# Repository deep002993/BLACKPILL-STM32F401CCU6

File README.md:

Title: BlackPill STM32F401CCU6 KiCad PCB Design

Description:
This repository hosts a KiCad PCB design for the STM32F401CCU6 microcontroller board, commonly known as BlackPill. Featuring a meticulously crafted layout and detailed schematic, it's optimized for affordability and performance, ideal for embedded projects. With comprehensive documentation and open-source licensing, it's ready for seamless integration and customization in your designs.

Features:
- Detailed Schematic & Layout
- Component Libraries Included
- Comprehensive Documentation
- Open Source & Customizable

Get Started:
Clone or download the repository to access the design files. Integrate seamlessly into your KiCad projects and customize as needed. Join the community to contribute or seek assistance.

Let's innovate with BlackPill STM32F401CCU6 KiCad PCB design!

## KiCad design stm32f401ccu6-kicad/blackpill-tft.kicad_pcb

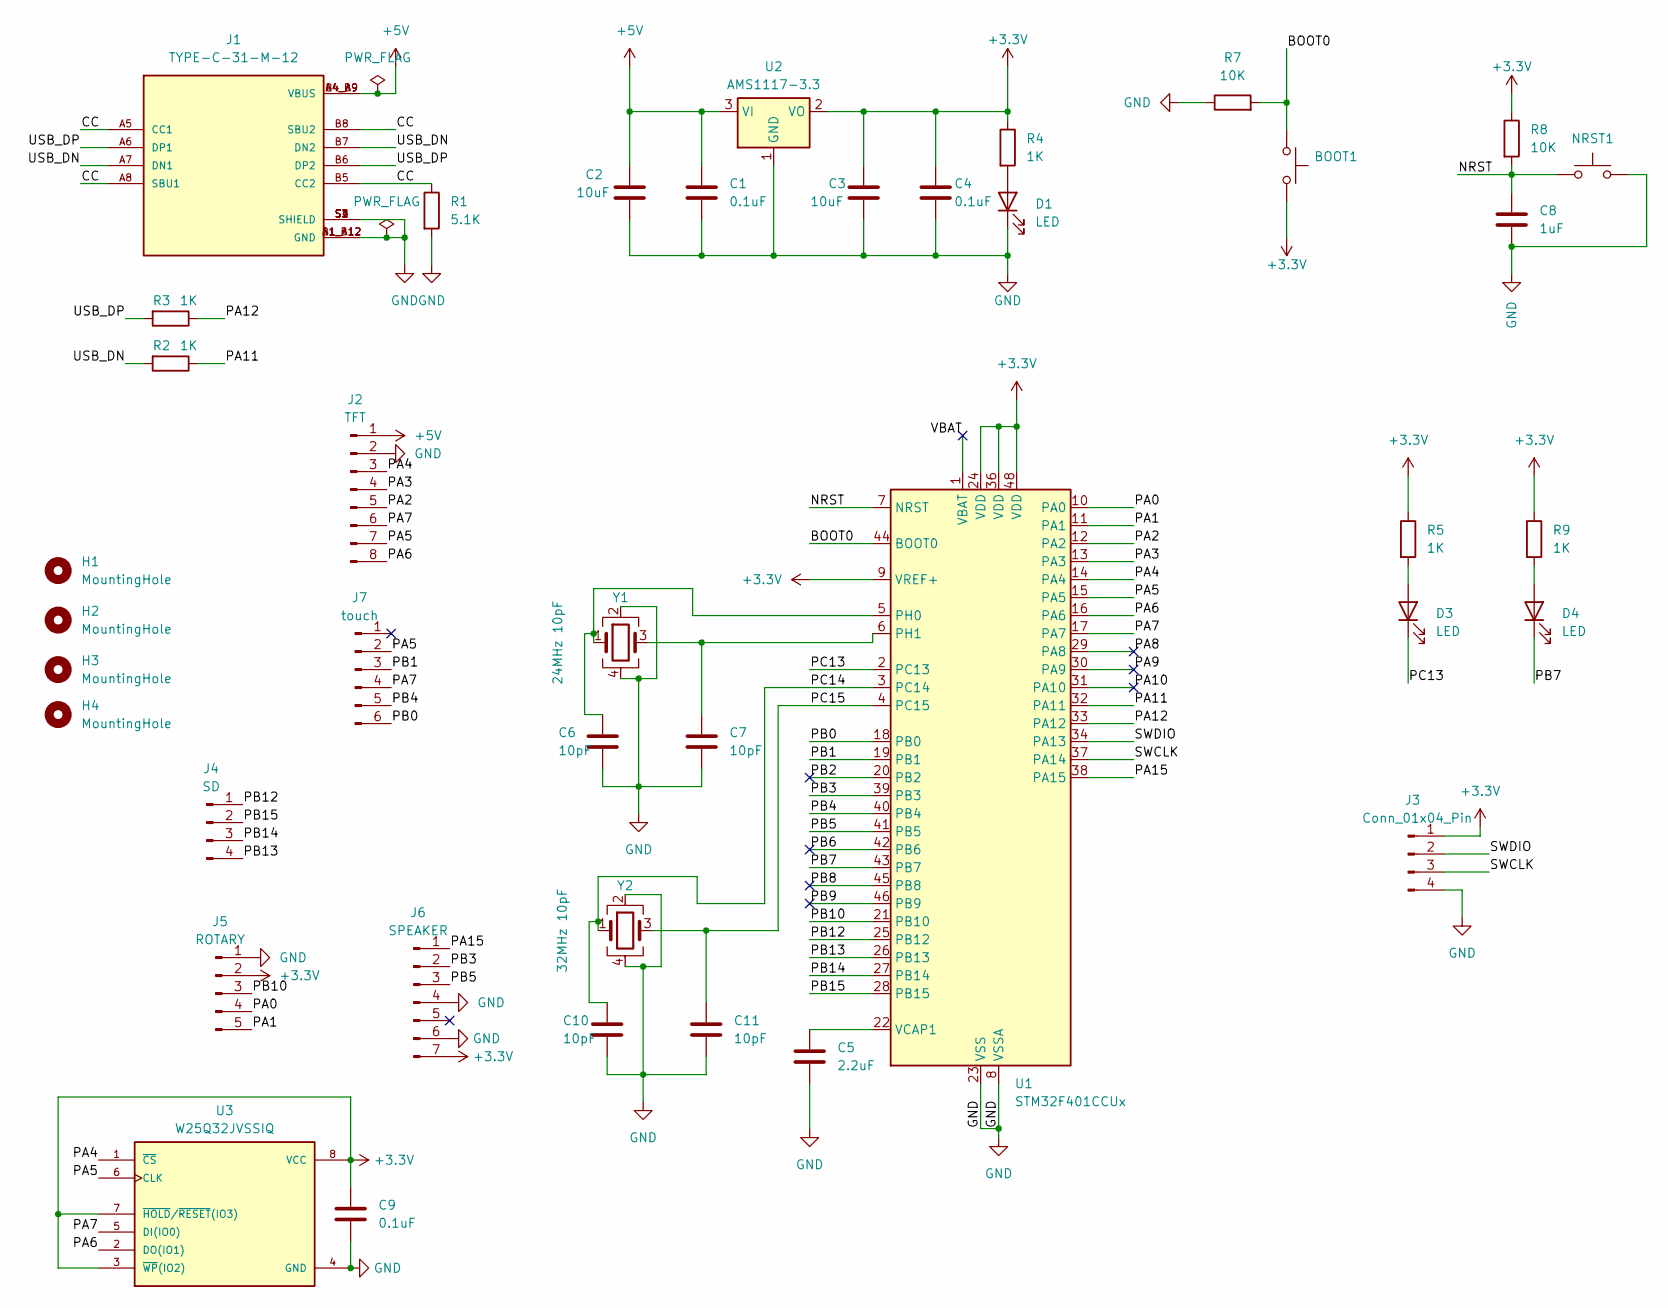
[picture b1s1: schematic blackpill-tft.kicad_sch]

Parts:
BOOT1: SW_DIP_x01; SW_Push_SPST_NO_Alps_0306
C1, C4, C9: 0.1uF; C_0805_2012Metric
C2, C3: 10uF; C_0805_2012Metric
C5: 2.2uF; C_0805_2012Metric
C6, C7, C10, C11: 10pF; C_0805_2012Metric
C8: 1uF; C_0805_2012Metric
D1, D3, D4: LED; LED_0805_2012Metric
H1, H2, H3, H4: MountingHole; MountingHole_2.2mm_M2
J1: TYPE-C-31-M-12; HRO_TYPE-C-31-M-12; PARTREV 2020.12.08
J2: TFT; PinHeader_1x08_P2.54mm_Vertical
J3: Conn_01x04_Pin; PinHeader_1x04_P2.54mm_Vertical
J4: SD; PinSocket_1x04_P2.54mm_Vertical
J5: ROTARY; PinHeader_1x05_P2.54mm_Vertical
J6: SPEAKER; PinHeader_1x07_P2.54mm_Vertical
J7: touch; PinHeader_1x06_P2.54mm_Vertical
NRST1: SW_DIP_x01; SW_Push_SPST_NO_Alps_0306
R1: 5.1K; R_0805_2012Metric
R2, R3, R4, R5, R9: 1K; R_0805_2012Metric
R7, R8: 10K; R_0805_2012Metric
U1: STM32F401CCUx; LQFP-48-1EP_7x7mm_P0.5mm_EP3.6x3.6mm
U2: AMS1117-3.3; SOT-223-3_TabPin2
U3: W25Q32JVSSIQ; SOIC127P790X216-8N
Y1: 24MHz 10pF; OSC_XRCGB24M000F2P01R0
Y2: 32MHz 10pF; OSC_XRCGB24M000F2P01R0

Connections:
+3.3V: BOOT1.2, C3.1, C4.1, C9.1, J3.1, J5.2, J6.7, R4.1, R5.1, R8.1, R9.1, U1.9 (VREF+), U1.24 (VDD), U1.36 (VDD), U1.48 (VDD), U2.2 (VO), U3.3 (~WP(IO2)), U3.7 (~HOLD/~RESET(IO3)), U3.8 (VCC)
+5V: C1.1, C2.1, J1.A4_B9 (VBUS), J1.B4_A9 (VBUS), J2.1, U2.3 (VI)
/BOOT0: BOOT1.1, R7.2, U1.44 (BOOT0)
/CC: J1.A5 (CC1), J1.A8 (SBU1), J1.B5 (CC2), J1.B8 (SBU2), R1.1
/NRST: C8.1, NRST1.1, R8.2, U1.7 (NRST)
/PA0: J5.4, U1.10 (PA0)
/PA1: J5.5, U1.11 (PA1)
/PA2: J2.5, U1.12 (PA2)
/PA3: J2.4, U1.13 (PA3)
/PA4: J2.3, U1.14 (PA4), U3.1 (~CS)
/PA5: J2.7, J7.2, U1.15 (PA5), U3.6 (CLK)
/PA6: J2.8, U1.16 (PA6), U3.2 (DO(IO1))
/PA7: J2.6, J7.4, U1.17 (PA7), U3.5 (DI(IO0))
/PA8: U1.29 (PA8)
/PA9: U1.30 (PA9)
/PA10: U1.31 (PA10)
/PA11: R2.1, U1.32 (PA11)
/PA12: R3.1, U1.33 (PA12)
/PA15: J6.1, U1.38 (PA15)
/PB0: J7.6, U1.18 (PB0)
/PB1: J7.3, U1.19 (PB1)
/PB2: U1.20 (PB2)
/PB3: J6.2, U1.39 (PB3)
/PB4: J7.5, U1.40 (PB4)
/PB5: J6.3, U1.41 (PB5)
/PB6: U1.42 (PB6)
/PB7: D4.1 (K), U1.43 (PB7)
/PB8: U1.45 (PB8)
/PB9: U1.46 (PB9)
/PB10: J5.3, U1.21 (PB10)
/PB12: J4.1, U1.25 (PB12)
/PB13: J4.4, U1.26 (PB13)
/PB14: J4.3, U1.27 (PB14)
/PB15: J4.2, U1.28 (PB15)
/PC13: D3.1 (K), U1.2 (PC13)
/PC14: C10.1, U1.3 (PC14), Y2.1
/PC15: C11.1, U1.4 (PC15), Y2.3
/SWCLK: J3.3, U1.37 (PA14)
/SWDIO: J3.2, U1.34 (PA13)
/USB_DN: J1.A7 (DN1), J1.B7 (DN2), R2.2
/USB_DP: J1.A6 (DP1), J1.B6 (DP2), R3.2
/VBAT: U1.1 (VBAT)
GND: C1.2, C2.2, C3.2, C4.2, C5.2, C6.2, C7.2, C8.2, C9.2, C10.2, C11.2, D1.1 (K), J1.A1_B12 (GND), J1.B1_A12 (GND), J1.S1 (SHIELD), J1.S2 (SHIELD), J1.S3 (SHIELD), J1.S4 (SHIELD), J2.2, J3.4, J5.1, J6.4, J6.6, NRST1.2, R1.2, R7.1, U1.8 (VSSA), U1.23 (VSS), U1.35 (VSS), U1.47 (VSS), U1.49 (VSS), U2.1 (GND), U3.4 (GND), Y1.2, Y1.4, Y2.2, Y2.4
unnamed: D1.2 (A), R4.2
unnamed: D3.2 (A), R5.2
unnamed: D4.2 (A), R9.2
unnamed: C6.1, U1.5 (PH0), Y1.1
unnamed: C7.1, U1.6 (PH1), Y1.3
unnamed: C5.1, U1.22 (VCAP1)

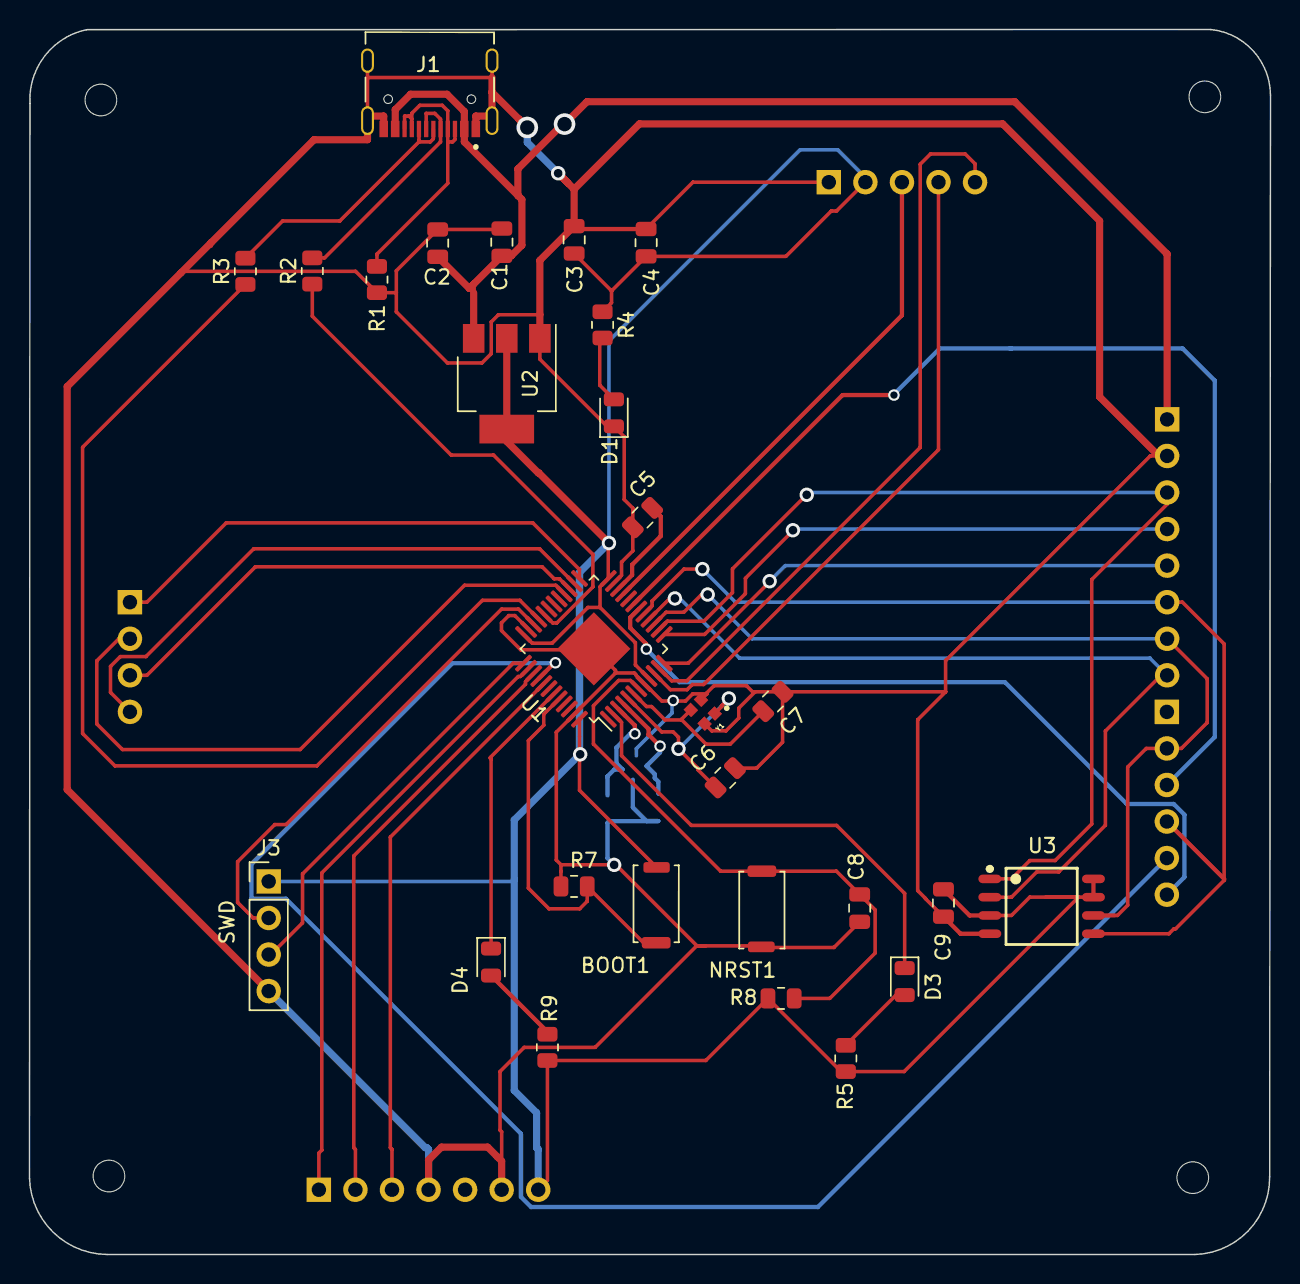
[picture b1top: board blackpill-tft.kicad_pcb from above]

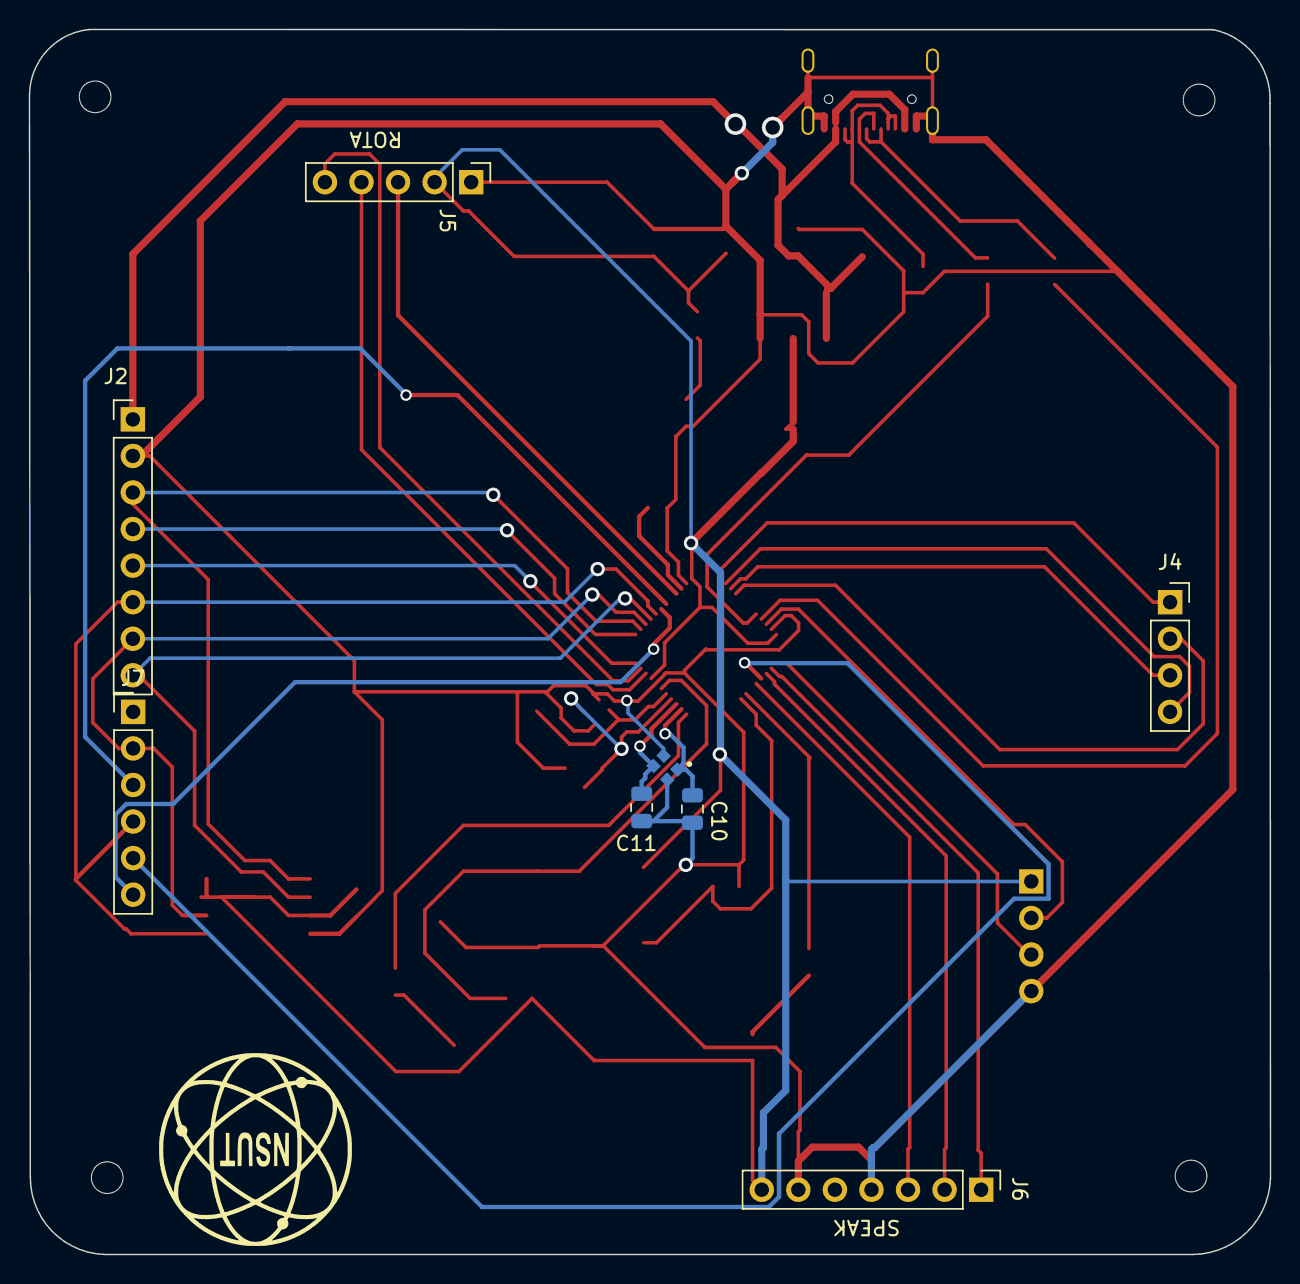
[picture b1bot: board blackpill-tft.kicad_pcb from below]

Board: 2 copper layers, 86.2 x 85.1 mm, 40 parts (8 on the bottom side), 41 nets.
